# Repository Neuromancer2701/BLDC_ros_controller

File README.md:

BLDC_ROS_controller
===================

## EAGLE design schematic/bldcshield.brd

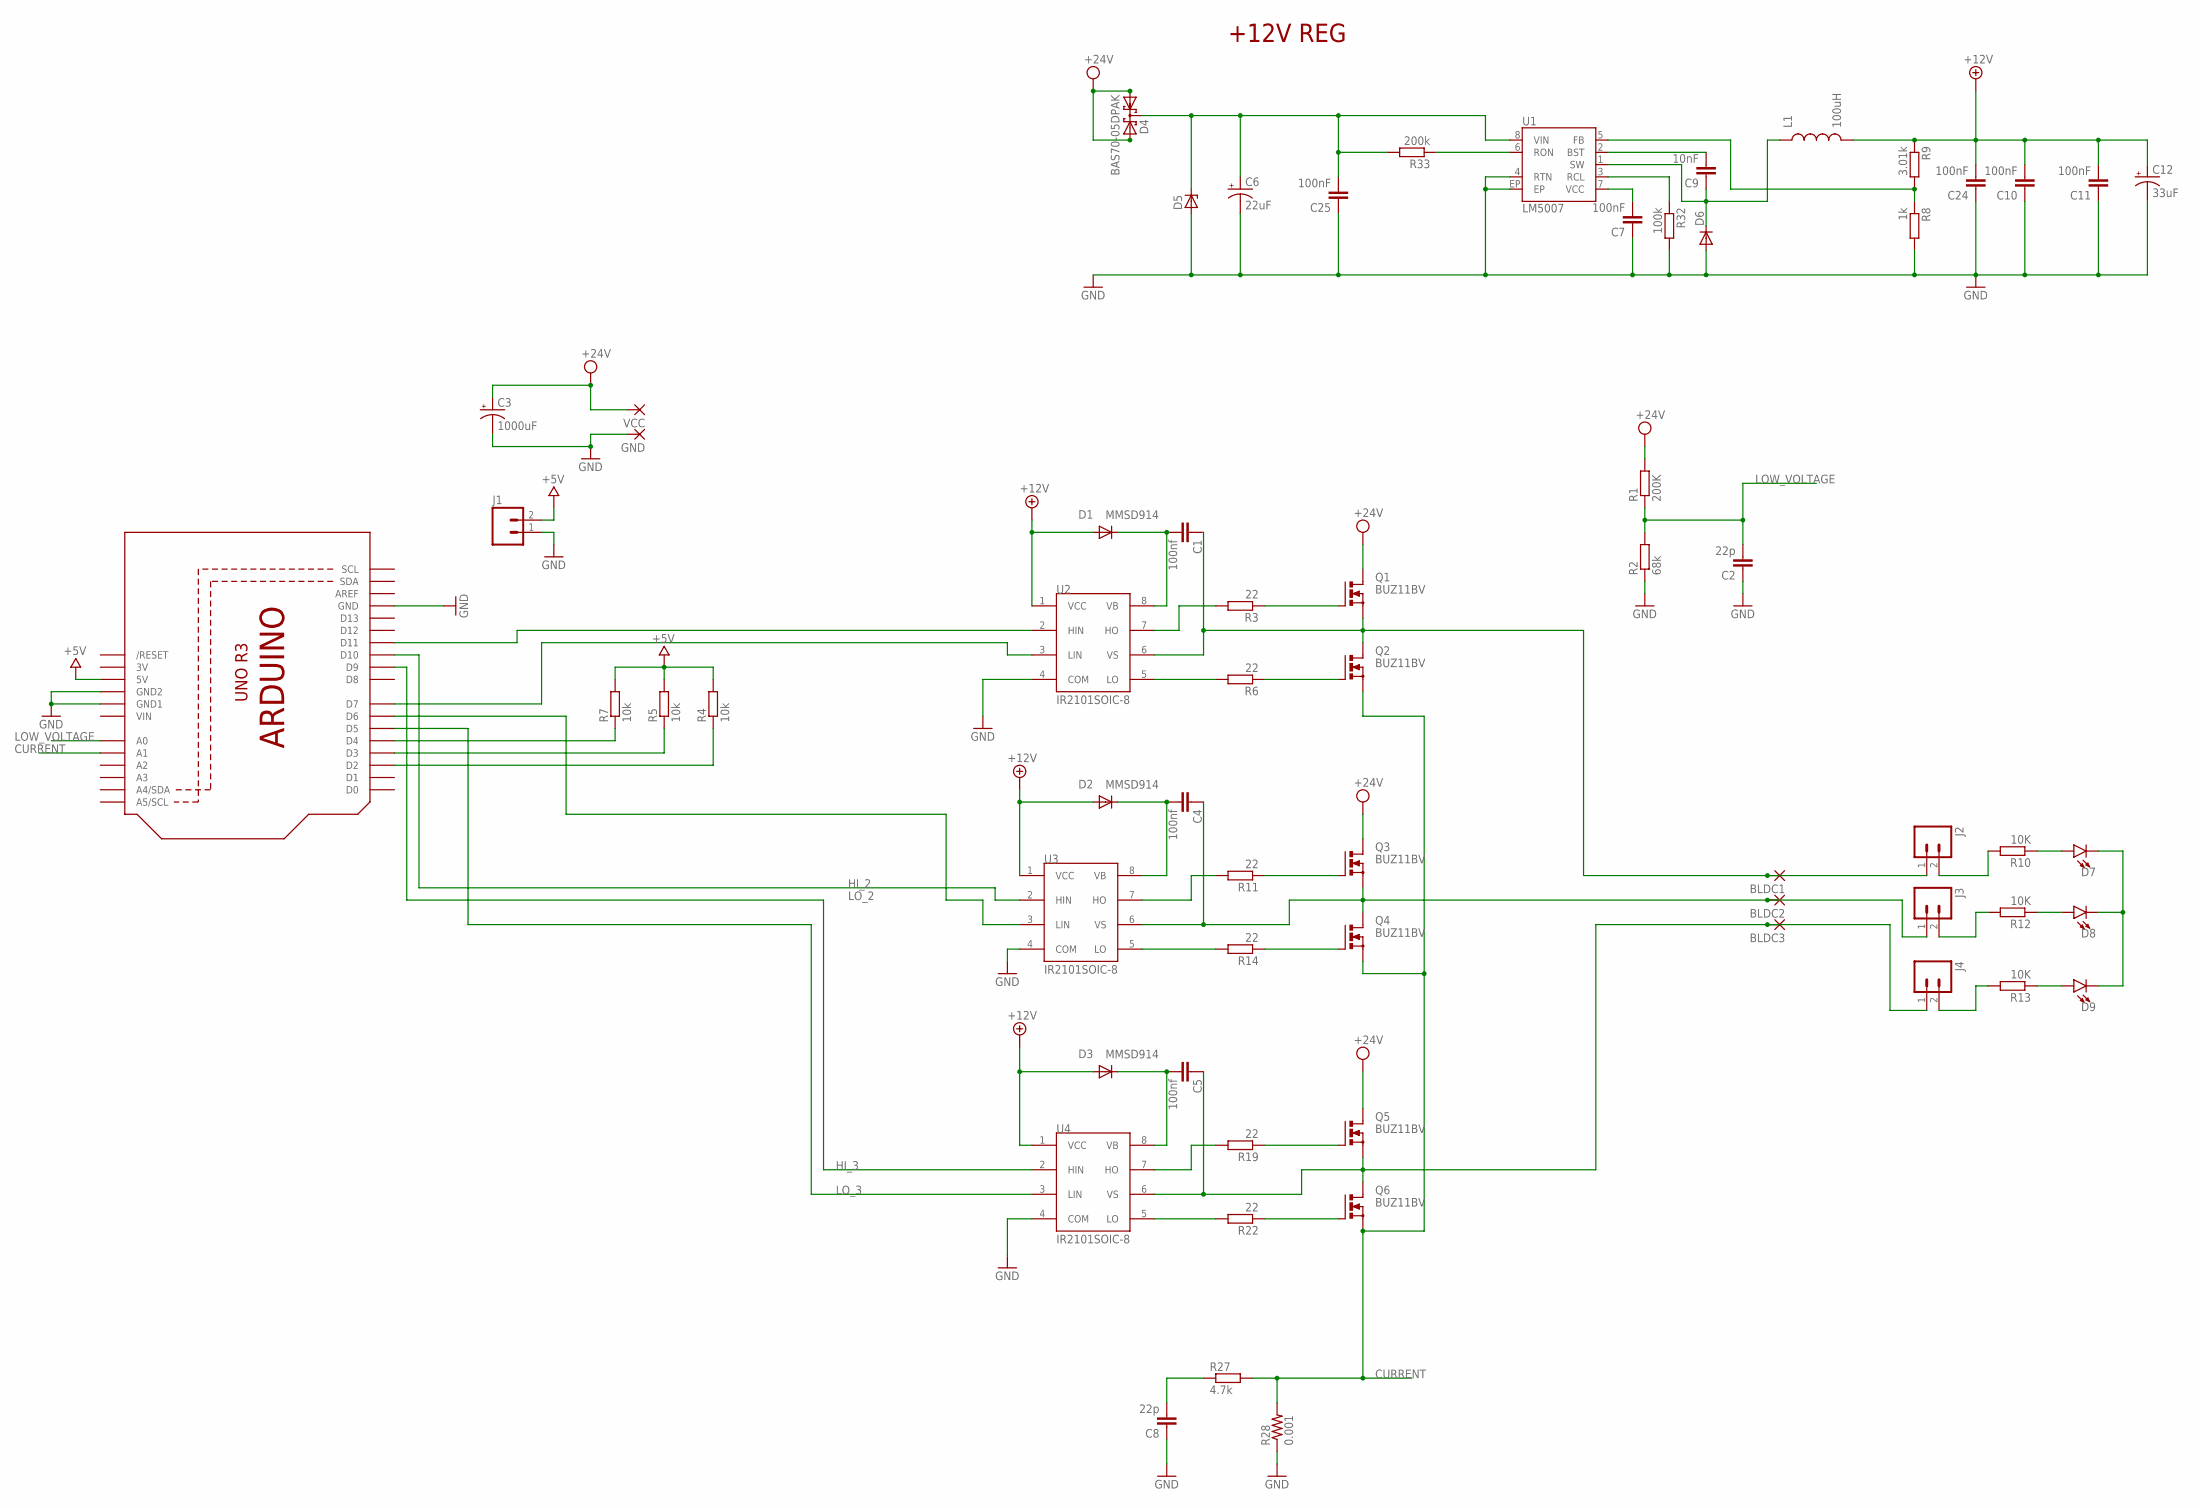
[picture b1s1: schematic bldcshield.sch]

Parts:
BLDC1, BLDC2, BLDC3: WIREPAD4,16O1,6; 4,16O1,6
C1, C4, C5: 100nf; C1206
C2, C8: 22p; C1206
C3: 1000uF; CPOL-RADIAL-1000UF-63V
C6: 22uF; PANASONIC_C
C7, C10, C11, C24, C25: 100nF; C1206
C9: 10nF; C1206
C12: 33uF; PANASONIC_C
D1, D2, D3: MMSD914; SOD123
D4: BAS70-05DPAK; DPAK229P990X238-3N
D5: SMF43A; SOD123F
D6: MBR0520LT; SOD123
D7, D8, D9: LED5MM; LED_5MM
GND: WIREPAD4,16O1,6; 4,16O1,6
J1, J2, J3, J4: M02PTH; 1X02
L1: 100uH; INDUCTOR-SRP4020
Q1, Q2, Q3, Q4, Q5, Q6: BUZ11BV; TO220BV
Q8: Shield; ARDUINOR3-NOTEXT-NOIOREF
R1: 200K; R1206
R2: 68k; R1206
R3, R6, R11, R14, R19, R22: 22; R1206
R4, R5, R7: 10k; R1206
R8: 1k; R1206
R9: 3.01k; R1206
R10, R12, R13: 10K; R1206
R27: 4.7k; R1206
R28: 0.001; R2512
R32: 100k; R1206
R33: 200k; R1206
U1: LM5007; MSOP-8-EP
U2, U3, U4: IR2101SOIC-8; SOIC127P490X600X175-8N
VCC: WIREPAD4,16O1,6; 4,16O1,6

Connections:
3V: Q8.3V
+5V: J1.2, Q8.5V, R4.2, R5.2, R7.2
+12V: C10.2, C11.2, C12.+, C24.2, D1.A, D2.A, D3.A, L1.P$2 (2), R9.1, U2.1 (VCC), U3.1 (VCC), U4.1 (VCC)
BLDC1: BLDC1.1, C1.1, J2.1, Q1.S, Q2.D, U2.6 (VS)
BLDC2: BLDC2.1, C4.1, J3.1, Q3.S, Q4.D, U3.6 (VS)
BLDC3: BLDC3.1, C5.1, J4.1, Q5.S, Q6.D, U4.6 (VS)
CURRENT: Q2.S, Q4.S, Q6.S, Q8.A1, R27.2, R28.2
GND: C2.1, C3.2 (-), C6.-, C7.1, C8.1, C10.1, C11.1, C12.-, C24.1, C25.1, D5.A, D6.A, GND.1, J1.1, Q8.GND, Q8.GND1, Q8.GND2, R2.1, R8.2, R28.1, R32.2, U1.4 (RTN), U1.EP, U2.4 (COM), U3.4 (COM), U4.4 (COM)
HI_2: Q8.D10, U3.2 (HIN)
HI_3: Q8.D9, U4.2 (HIN)
LOW_VOLTAGE: C2.2, Q8.A0, R1.1, R2.2
LO_2: Q8.D6, U3.3 (LIN)
LO_3: Q8.D5, U4.3 (LIN)
unnamed: Q3.G, R11.1
unnamed: C6.+, C25.2, D4.4 (K1K2), D5.C, R33.2, U1.8 (VIN)
unnamed: Q8.D11, U2.2 (HIN)
unnamed: Q8.D4, R7.1
unnamed: Q8.D3, R5.1
unnamed: Q8.D2, R4.1
unnamed: Q8.D7, U2.3 (LIN)
unnamed: C8.2, R27.1
unnamed: R6.2, U2.5 (LO)
unnamed: R3.2, U2.7 (HO)
unnamed: R33.1, U1.6 (RON)
unnamed: R19.2, U4.7 (HO)
unnamed: Q5.G, R19.1
unnamed: Q6.G, R22.1
unnamed: R22.2, U4.5 (LO)
unnamed: C9.2, U1.2 (BST)
unnamed: C7.2, U1.7 (VCC)
unnamed: C9.1, D6.C, L1.P$1 (1), U1.1 (SW)
unnamed: R32.1, U1.3 (RCL)
unnamed: R11.2, U3.7 (HO)
unnamed: Q4.G, R14.1
unnamed: R14.2, U3.5 (LO)
unnamed: J2.2, R10.2
unnamed: R8.1, R9.2, U1.5 (FB)
unnamed: J3.2, R12.2
unnamed: J4.2, R13.2
unnamed: D7.A, R10.1
unnamed: Q1.G, R3.1
unnamed: Q2.G, R6.1
unnamed: D8.A, R12.1
unnamed: D9.A, R13.1
unnamed: D7.K (C), D8.K (C), D9.K (C)
VB1: C1.2, D1.C, U2.8 (VB)
VB2: C4.2, D2.C, U3.8 (VB)
VB3: C5.2, D3.C, U4.8 (VB)
VCC: C3.1 (+), D4.1 (A1), D4.3 (A2), Q1.D, Q3.D, Q5.D, R1.2, VCC.1
VIN: Q8.VIN

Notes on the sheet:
+12V REG

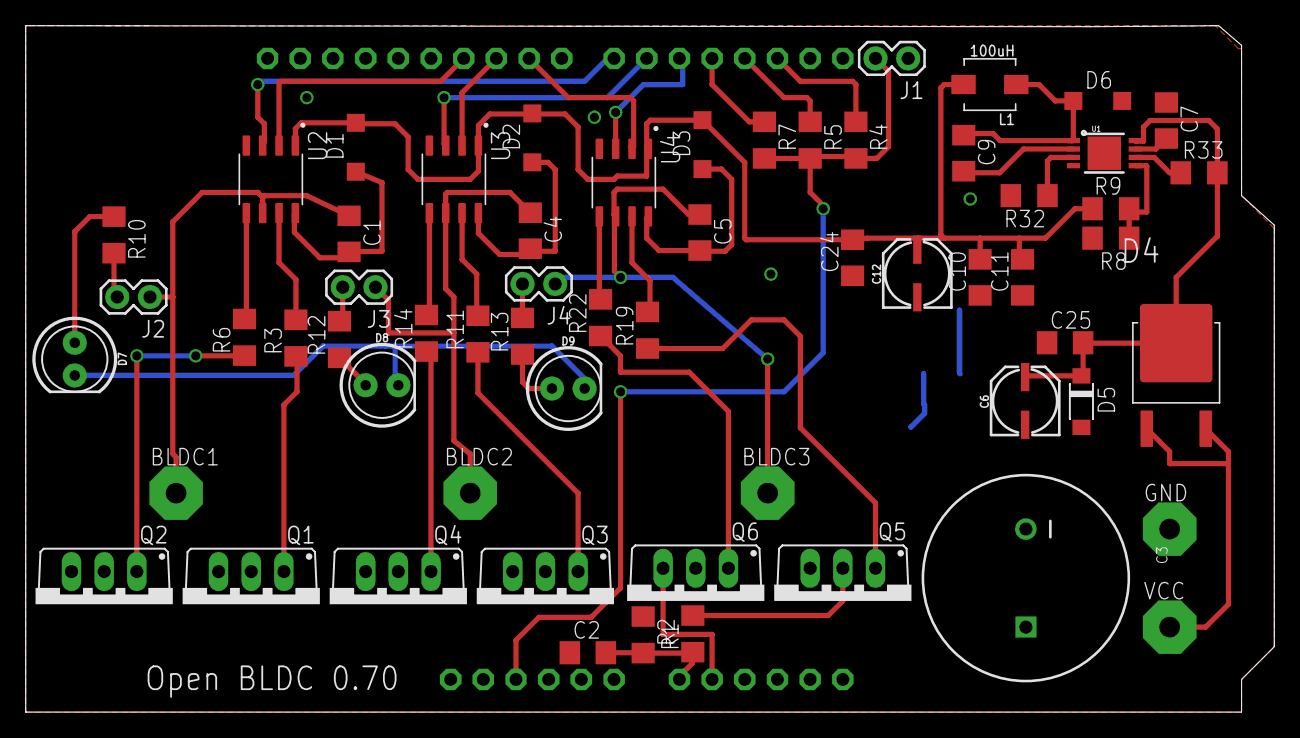
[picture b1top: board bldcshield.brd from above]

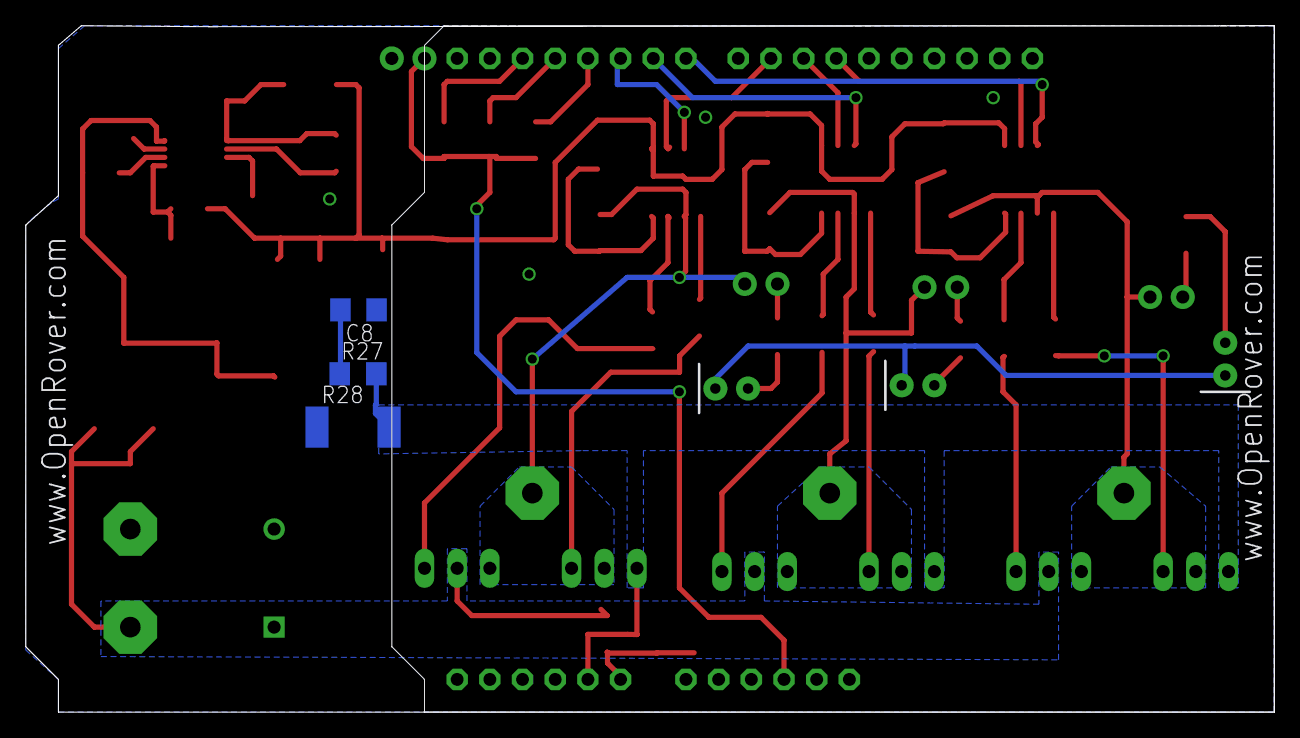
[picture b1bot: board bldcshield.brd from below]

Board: 2 copper layers, 97.0 x 53.3 mm, 64 parts (3 on the bottom side), 48 nets.

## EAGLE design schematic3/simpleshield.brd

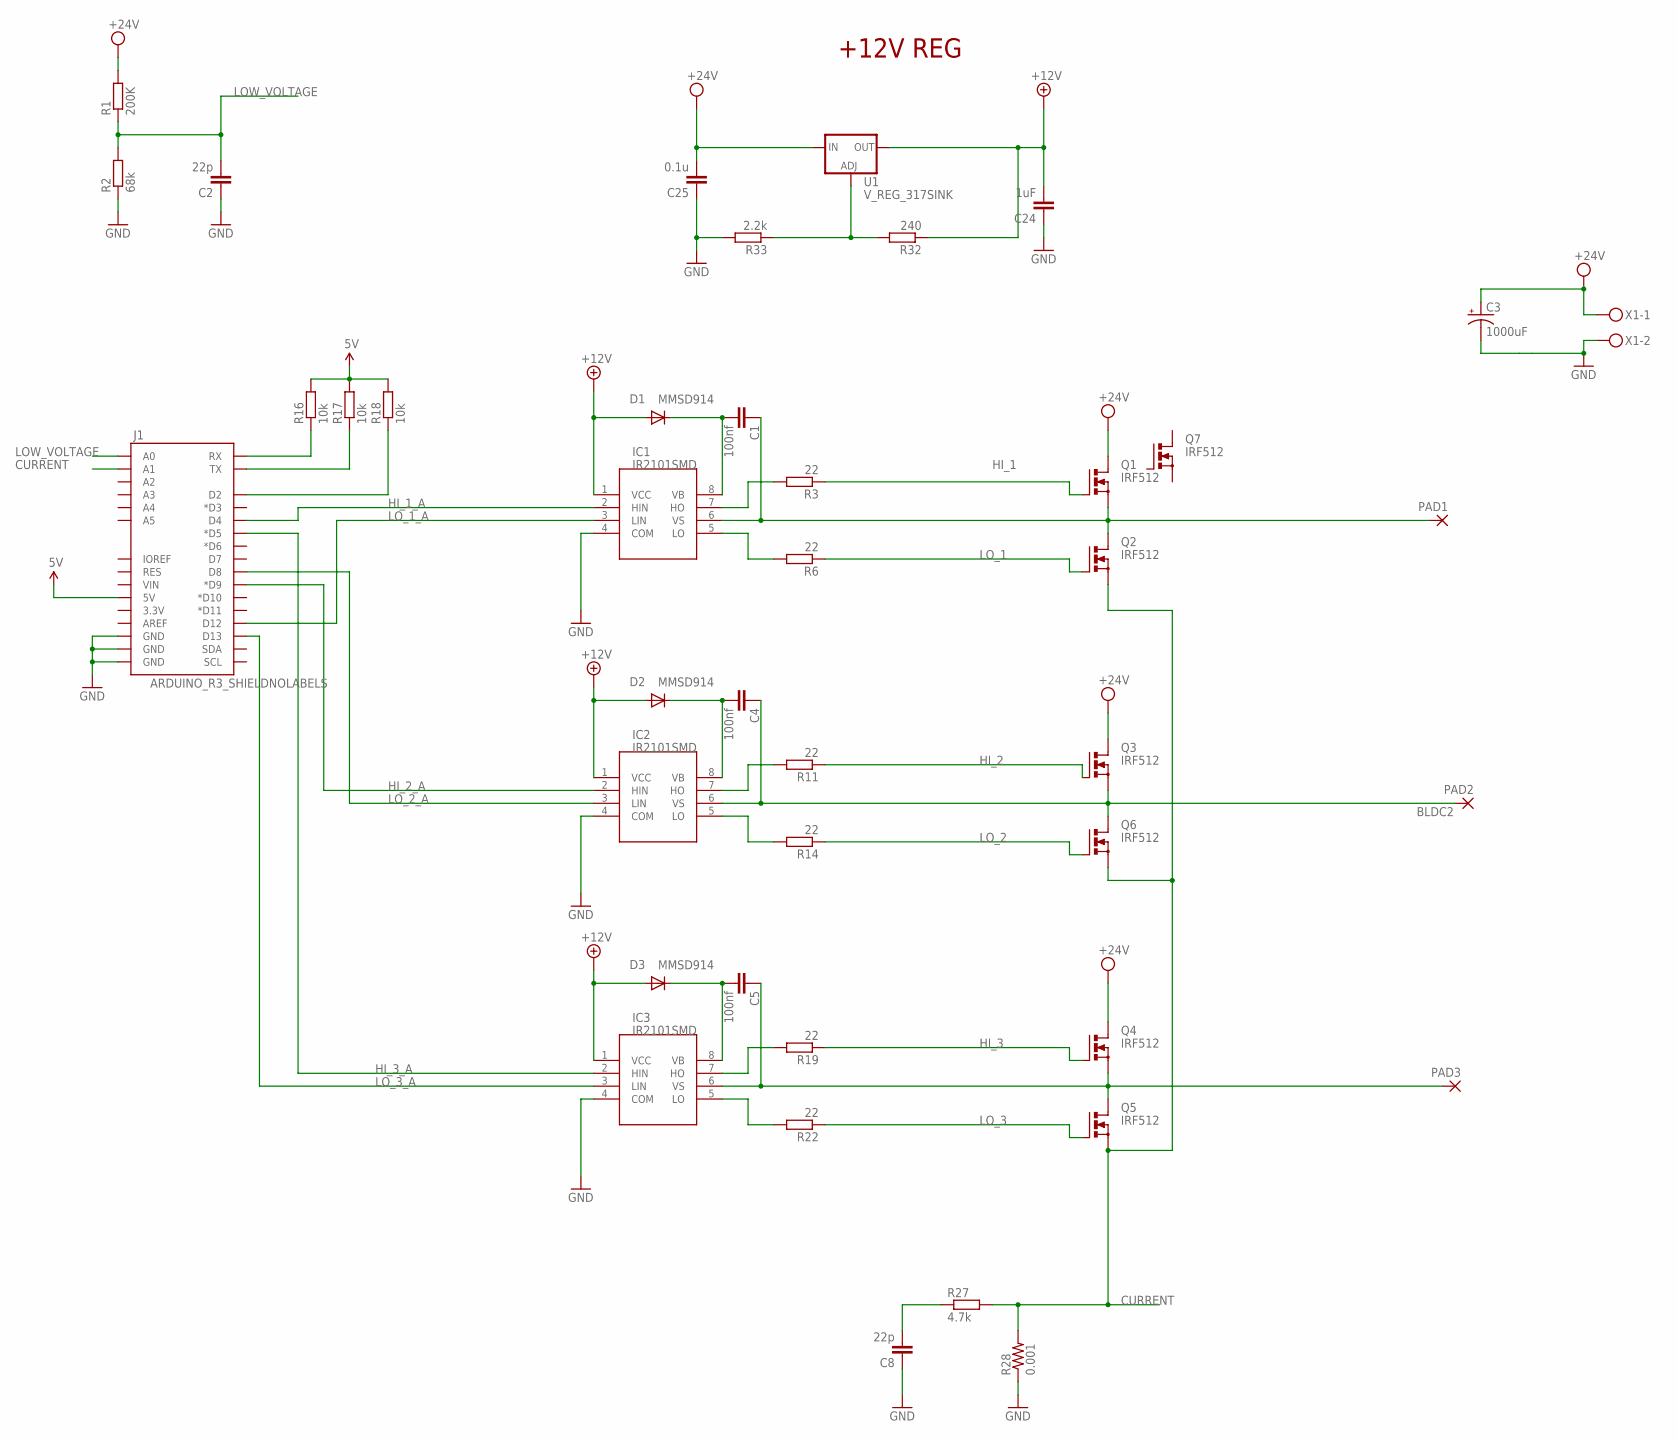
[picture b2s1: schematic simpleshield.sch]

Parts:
C1, C4, C5: 100nf; C1206
C2, C8: 22p; C1206
C3: 1000uF; CPOL-RADIAL-1000UF-63V
C24: 1uF; C1206
C25: 0.1u; C1206
D1, D2, D3: MMSD914; SOD123
IC1, IC2, IC3: IR2101SMD; SO08
J1: ARDUINO_R3_SHIELDNOLABELS; UNO_R3_SHIELD_NOLABELS
PAD1, PAD2, PAD3: 3,81/1,4
Q1, Q2, Q3, Q4, Q5, Q6, Q7: IRF512; TO220BV
R1: 200K; R1206
R2: 68k; R1206
R3, R6, R11, R14, R19, R22: 22; R1206
R16, R17, R18: 10k; R1206
R27: 4.7k; R1206
R28: 0.001; R2512
R32: 240; R1206
R33: 2.2k; R1206
U1: V_REG_317SINK; TO220-ADJ
X1: MKDSN1,5/2-5,08

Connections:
5V: J1.5V, R16.2, R17.2, R18.2
+12V: C24.2, D1.A, D2.A, D3.A, IC1.1 (VCC), IC2.1 (VCC), IC3.1 (VCC), R32.1, U1.OUT
BLDC1: C1.1, IC1.6 (VS), PAD1.1, Q1.S, Q2.D
BLDC2: C4.1, IC2.6 (VS), PAD2.1, Q3.S, Q6.D
BLDC3: C5.1, IC3.6 (VS), PAD3.1, Q4.S, Q5.D
CURRENT: J1.A1, Q2.S, Q5.S, Q6.S, R27.2, R28.2
GND: C2.1, C3.2 (-), C8.1, C24.1, C25.1, IC1.4 (COM), IC2.4 (COM), IC3.4 (COM), J1.GND@0 (GND), J1.GND@1 (GND), J1.GND@2 (GND), R2.1, R28.1, R33.2, X1.2
HI_1: Q1.G, R3.1
HI_1_A: IC1.2 (HIN), J1.D4
HI_2: Q3.G, R11.1
HI_2_A: IC2.2 (HIN), J1.D9 (*D9)
HI_3: Q4.G, R19.1
HI_3_A: IC3.2 (HIN), J1.D5 (*D5)
LOW_VOLTAGE: C2.2, J1.A0, R1.1, R2.2
LO_1: Q2.G, R6.1
LO_1_A: IC1.3 (LIN), J1.D12
LO_2: Q6.G, R14.1
LO_2_A: IC2.3 (LIN), J1.D8
LO_3: Q5.G, R22.1
LO_3_A: IC3.3 (LIN), J1.D13
unnamed: J1.RX, R16.1
unnamed: R32.2, R33.1, U1.ADJ
unnamed: J1.TX, R17.1
unnamed: J1.D2, R18.1
unnamed: C8.2, R27.1
unnamed: IC3.7 (HO), R19.2
unnamed: IC3.5 (LO), R22.2
unnamed: C5.2, D3.C, IC3.8 (VB)
unnamed: IC2.7 (HO), R11.2
unnamed: IC2.5 (LO), R14.2
unnamed: C4.2, D2.C, IC2.8 (VB)
unnamed: IC1.7 (HO), R3.2
unnamed: IC1.5 (LO), R6.2
unnamed: C1.2, D1.C, IC1.8 (VB)
VCC: C3.1 (+), C25.2, Q1.D, Q3.D, Q4.D, R1.2, U1.IN, X1.1

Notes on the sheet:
+12V REG

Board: 2 copper layers, 42 parts (0 on the bottom side), 35 nets, no tracks yet.

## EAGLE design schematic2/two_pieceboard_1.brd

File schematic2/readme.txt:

By using or installing (as applicable) this package, you accept all the terms of the Reference Material
license agreement available at : www.st.com/opla

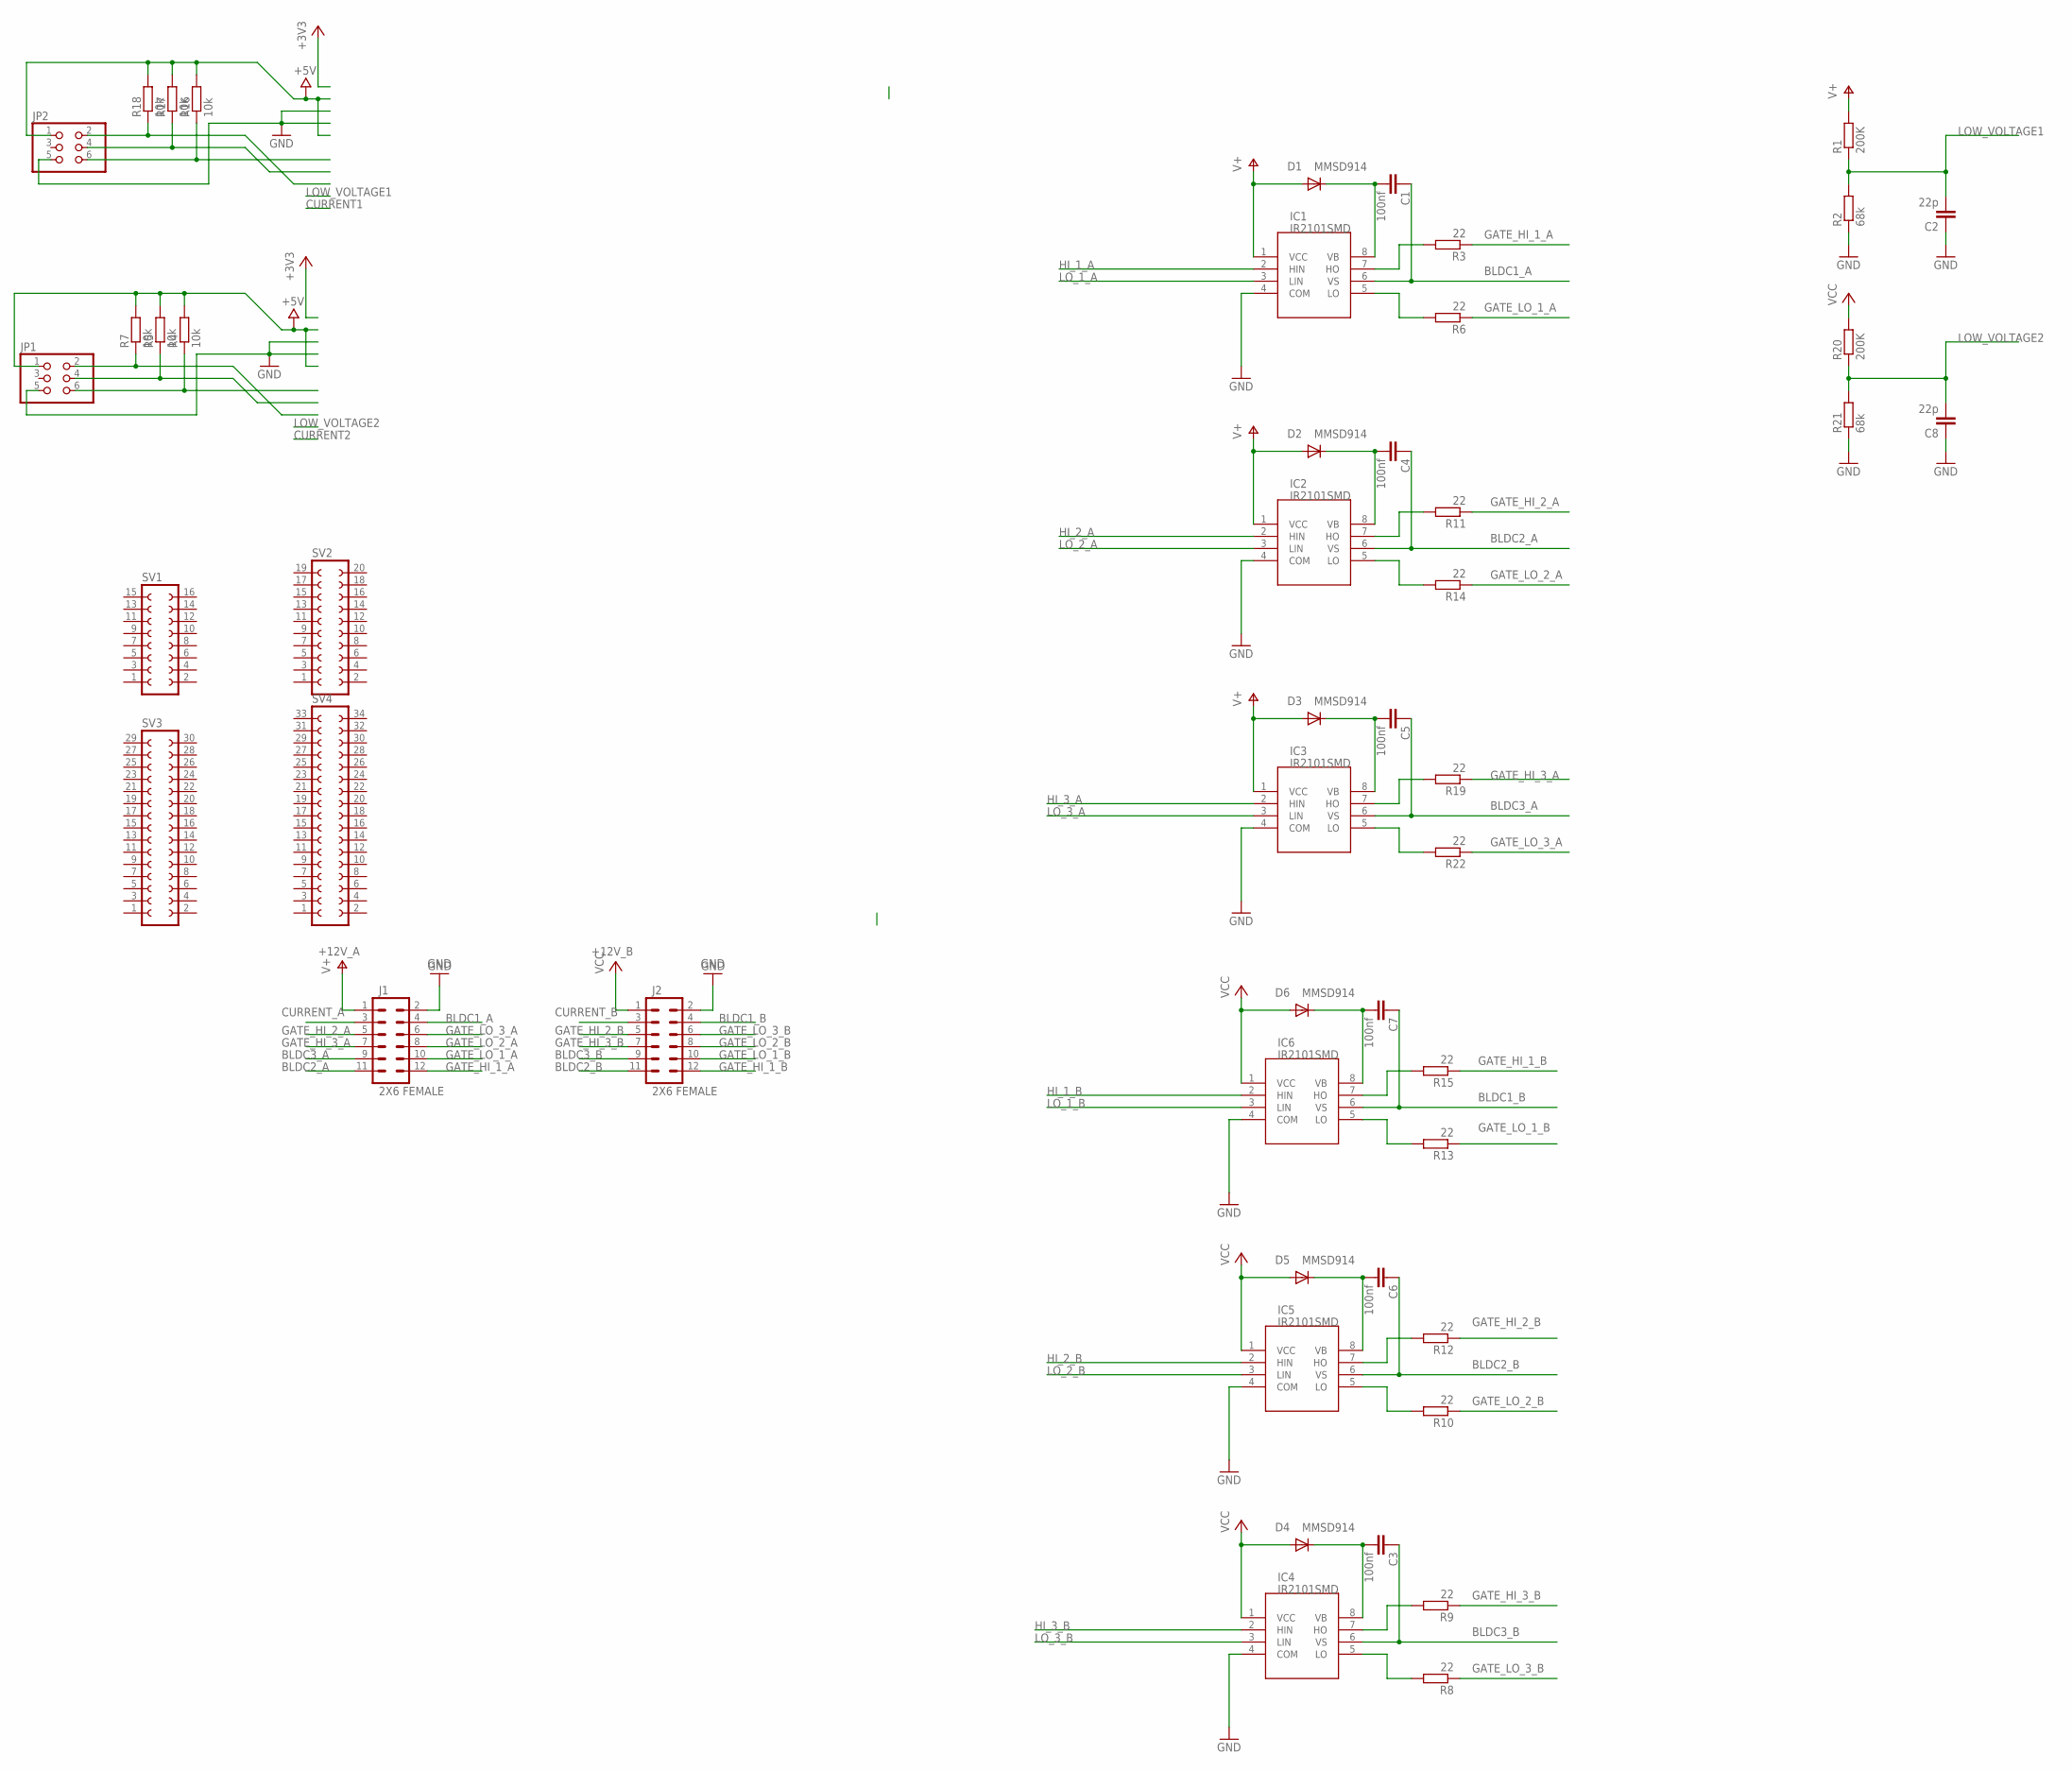
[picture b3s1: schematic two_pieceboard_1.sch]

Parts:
C1, C3, C4, C5, C6, C7: 100nf; C1206
C2, C8: 22p; C1206
D1, D2, D3, D4, D5, D6: MMSD914; SOD123
IC1, IC2, IC3, IC4, IC5, IC6: IR2101SMD; SO08
J1, J2: 2X6 FEMALE; 2X6
JP1, JP2: PINHD-2X3; 2X03
R1, R20: 200K; R1206
R2, R21: 68k; R1206
R3, R6, R8, R9, R10, R11, R12, R13, R14, R15, R19, R22: 22; R1206
R4, R5, R7, R16, R17, R18: 10k; R1206
SV1: FE08-2
SV2: FE10-2
SV3: FE15-2
SV4: FE17-2

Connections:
+5V: JP1.1, JP2.1, R4.2, R5.2, R7.2, R16.2, R17.2, R18.2
+12V_A: D1.A, D2.A, D3.A, IC1.1 (VCC), IC2.1 (VCC), IC3.1 (VCC), J1.1, R1.2
+12V_B: D4.A, D5.A, D6.A, IC4.1 (VCC), IC5.1 (VCC), IC6.1 (VCC), J2.1, R20.2
BLDC1_A: C1.1, IC1.6 (VS), J1.4
BLDC1_B: C7.1, IC6.6 (VS), J2.4
BLDC2_A: C4.1, IC2.6 (VS), J1.11
BLDC2_B: C6.1, IC5.6 (VS), J2.11
BLDC3_A: C5.1, IC3.6 (VS), J1.9
BLDC3_B: C3.1, IC4.6 (VS), J2.9
CURRENT_A: J1.3
CURRENT_B: J2.3
GATE_HI_1_A: J1.12, R3.1
GATE_HI_1_B: J2.12, R15.1
GATE_HI_2_A: J1.5, R11.1
GATE_HI_2_B: J2.5, R12.1
GATE_HI_3_A: J1.7, R19.1
GATE_HI_3_B: J2.7, R9.1
GATE_LO_1_A: J1.10, R6.1
GATE_LO_1_B: J2.10, R13.1
GATE_LO_2_A: J1.8, R14.1
GATE_LO_2_B: J2.8, R10.1
GATE_LO_3_A: J1.6, R22.1
GATE_LO_3_B: J2.6, R8.1
GND: C2.1, C8.1, IC1.4 (COM), IC2.4 (COM), IC3.4 (COM), IC4.4 (COM), IC5.4 (COM), IC6.4 (COM), J1.2, J2.2, JP1.5, JP2.5, R2.1, R21.1
HI_1_A: IC1.2 (HIN)
HI_1_B: IC6.2 (HIN)
HI_2_A: IC2.2 (HIN)
HI_2_B: IC5.2 (HIN)
HI_3_A: IC3.2 (HIN)
HI_3_B: IC4.2 (HIN)
LOW_VOLTAGE1: C2.2, R1.1, R2.2
LOW_VOLTAGE2: C8.2, R20.1, R21.2
LO_1_A: IC1.3 (LIN)
LO_1_B: IC6.3 (LIN)
LO_2_A: IC2.3 (LIN)
LO_2_B: IC5.3 (LIN)
LO_3_A: IC3.3 (LIN)
LO_3_B: IC4.3 (LIN)
unnamed: JP1.2, R7.1
unnamed: JP1.6, R4.1
unnamed: IC4.7 (HO), R9.2
unnamed: JP1.4, R5.1
unnamed: IC4.5 (LO), R8.2
unnamed: IC3.7 (HO), R19.2
unnamed: IC3.5 (LO), R22.2
unnamed: C5.2, D3.C, IC3.8 (VB)
unnamed: C3.2, D4.C, IC4.8 (VB)
unnamed: IC5.7 (HO), R12.2
unnamed: IC2.7 (HO), R11.2
unnamed: IC5.5 (LO), R10.2
unnamed: IC2.5 (LO), R14.2
unnamed: C4.2, D2.C, IC2.8 (VB)
unnamed: C6.2, D5.C, IC5.8 (VB)
unnamed: IC6.7 (HO), R15.2
unnamed: IC1.7 (HO), R3.2
unnamed: IC6.5 (LO), R13.2
unnamed: IC1.5 (LO), R6.2
unnamed: C1.2, D1.C, IC1.8 (VB)
unnamed: C7.2, D6.C, IC6.8 (VB)
unnamed: JP2.6, R16.1
unnamed: JP2.4, R17.1
unnamed: JP2.2, R18.1

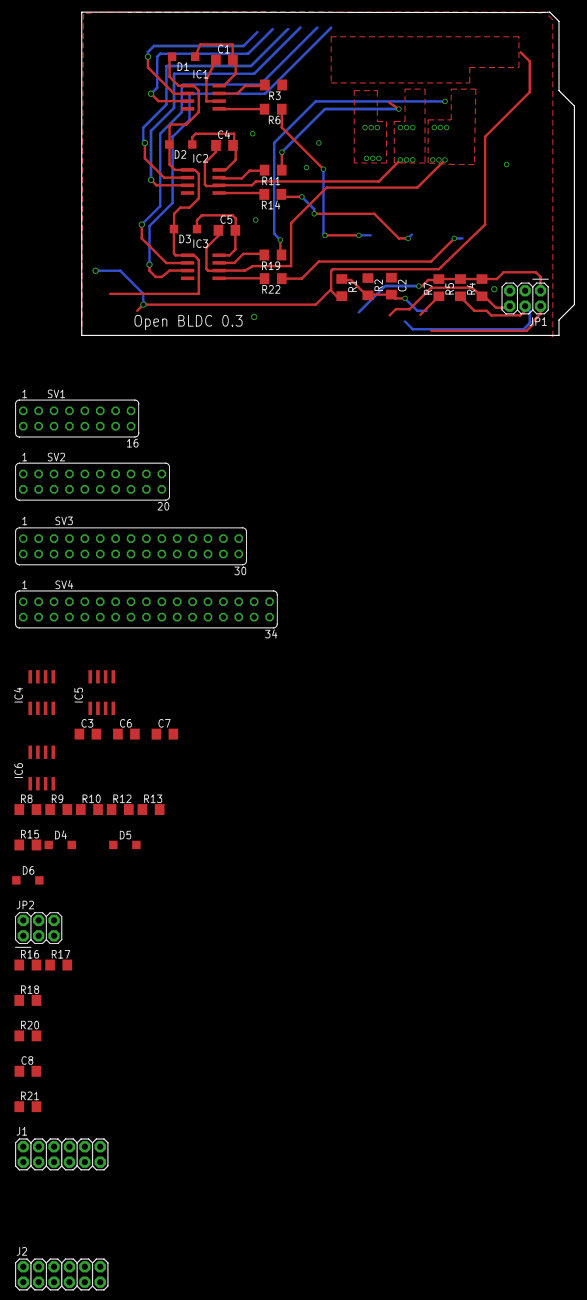
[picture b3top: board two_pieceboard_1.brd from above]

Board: 2 copper layers, 81.3 x 53.3 mm, 50 parts (0 on the bottom side), 48 nets.

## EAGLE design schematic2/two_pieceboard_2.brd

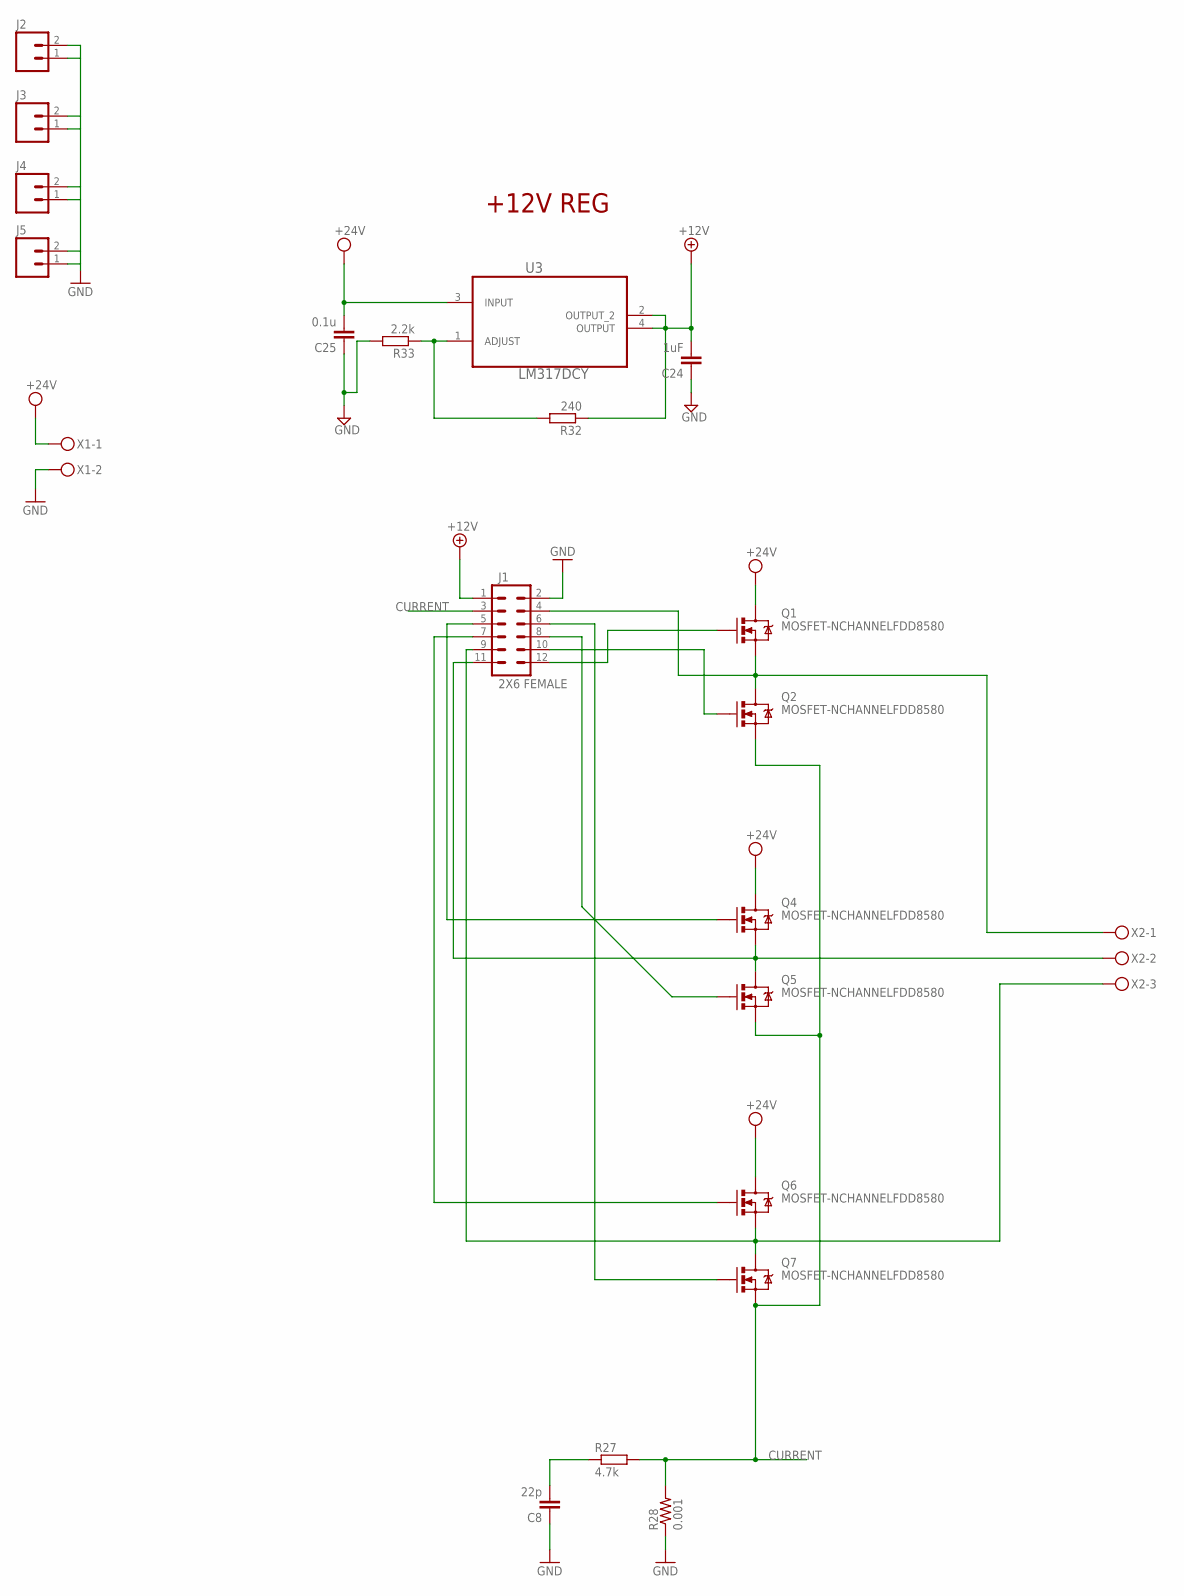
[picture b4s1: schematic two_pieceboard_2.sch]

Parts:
C8: 22p; C1206
C24: 1uF; C1206
C25: 0.1u; C1206
J1: 2X6 FEMALE; 2X6
J2, J3, J4, J5: M02PTH; 1X02
Q1, Q2, Q4, Q5, Q6, Q7: MOSFET-NCHANNELFDD8580; DPAK
R27: 4.7k; R1206
R28: 0.001; R2512
R32: 240; R1206
R33: 2.2k; R1206
U3: LM317DCY; SOT230P700X180-4N
X1: MKDSN1,5/2-5,08
X2: MKDSN1,5/3-5,08

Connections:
+12V: C24.2, J1.1, R32.1, U3.2 (OUTPUT_2), U3.4 (OUTPUT)
BLDC1: J1.4, Q1.3 (S), Q2.4 (D), X2.1
BLDC2: J1.11, Q4.3 (S), Q5.4 (D), X2.2
BLDC3: J1.9, Q6.3 (S), Q7.4 (D), X2.3
CURRENT: J1.3, Q2.3 (S), Q5.3 (S), Q7.3 (S), R27.2, R28.2
GND: C8.1, C24.1, C25.1, J1.2, J2.1, J2.2, J3.1, J3.2, J4.1, J4.2, J5.1, J5.2, R28.1, R33.2, X1.2
unnamed: J1.12, Q1.1 (G)
unnamed: J1.10, Q2.1 (G)
unnamed: R32.2, R33.1, U3.1 (ADJUST)
unnamed: J1.8, Q5.1 (G)
unnamed: J1.7, Q6.1 (G)
unnamed: J1.6, Q7.1 (G)
unnamed: C8.2, R27.1
unnamed: J1.5, Q4.1 (G)
VCC: C25.2, Q1.4 (D), Q4.4 (D), Q6.4 (D), U3.3 (INPUT), X1.1

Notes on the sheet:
+12V REG

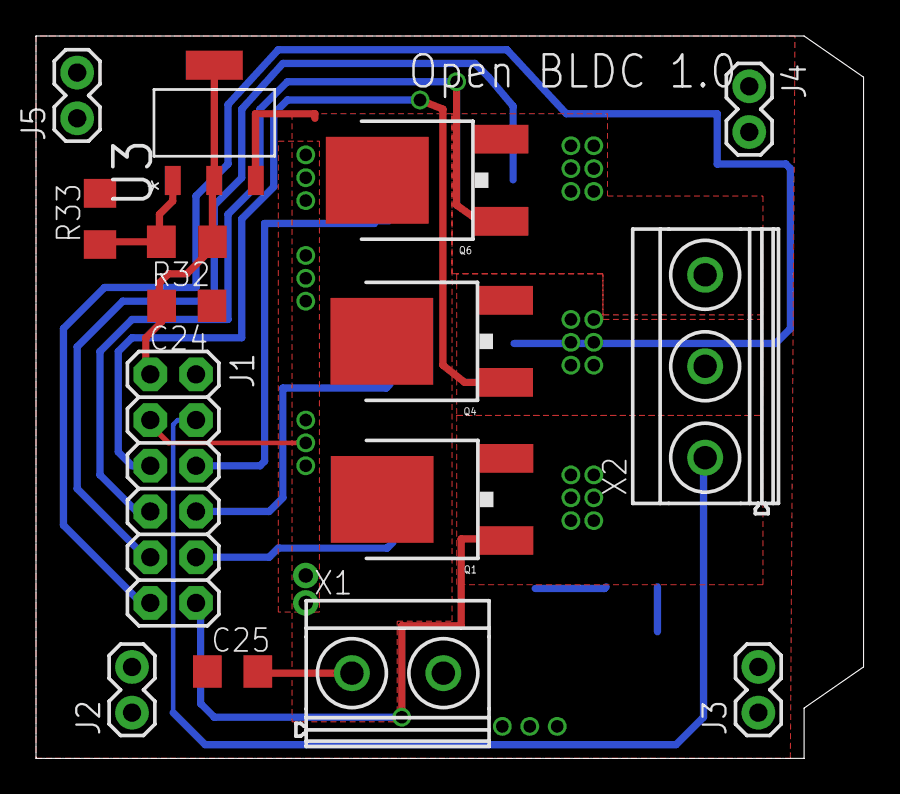
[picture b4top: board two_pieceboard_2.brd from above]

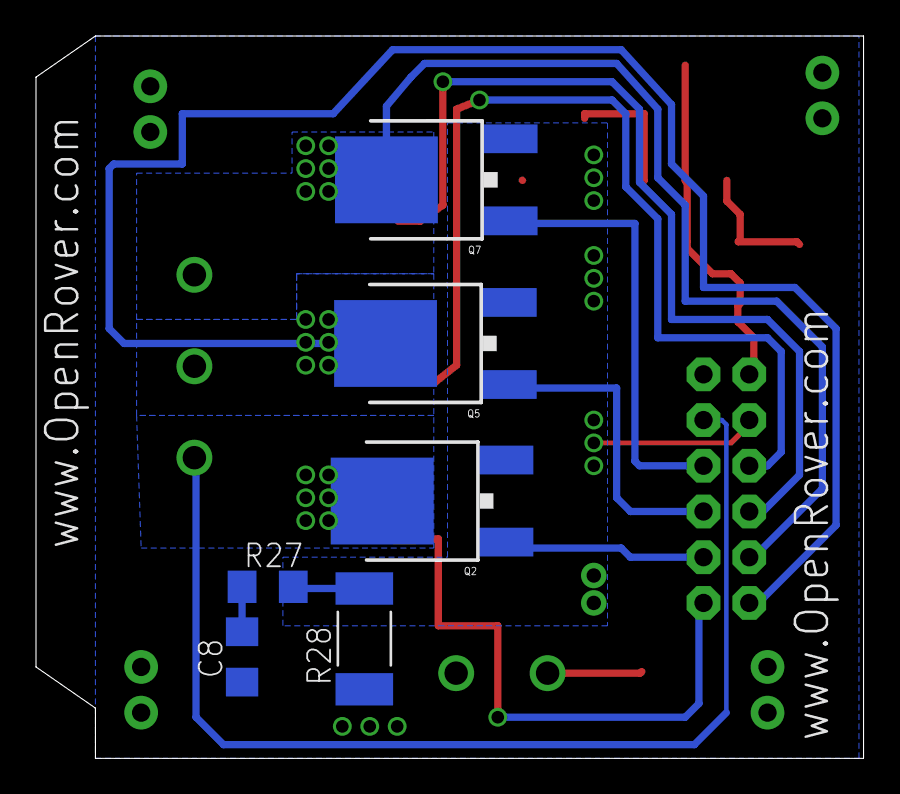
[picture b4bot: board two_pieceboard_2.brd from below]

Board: 2 copper layers, 46.0 x 40.1 mm, 21 parts (6 on the bottom side), 15 nets.

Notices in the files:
parts and their libraries:
SparkFun-Passives: Licensing: Creative Commons ShareAlike 4.0 International - https://creativecommons.org/licenses/by-sa/4.0
SparkFun: Licensing: CC v3.0 Share-Alike You are welcome to use this library for commercial purposes.
